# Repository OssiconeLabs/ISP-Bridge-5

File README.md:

# ISP-Bridge-5
ISP Bridge 5(Atmel ATtiny x8, ATmega x8)  
Source files from KiCad 4.0.2-stable, release build
-----
http://ossiconelabs.com  

Available to Buy at https://www.tindie.com/products/OssiconeLabs/isp-bridge-5atmel-attiny-x8-atmega-x8/  
Assembly Instructions at http://ossiconelabs.com/documentation/ISP_Bridge_5_Instructions_v2.0.pdf

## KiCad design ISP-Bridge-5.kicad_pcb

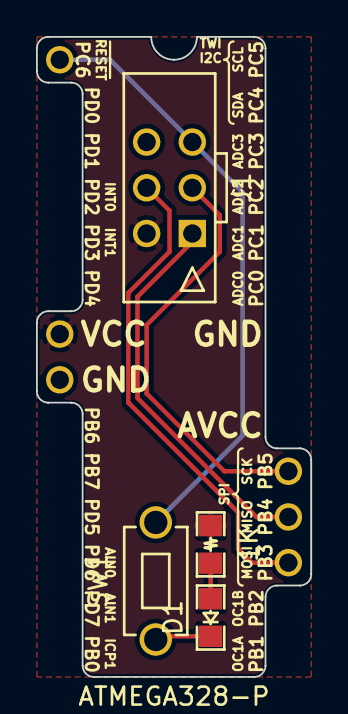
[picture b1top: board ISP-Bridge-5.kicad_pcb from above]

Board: 2 copper layers, 15.2 x 35.6 mm, 6 parts (0 on the bottom side), 7 nets.

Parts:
D1: LED; LED_0805_Symbol
IC1: ATMEGA328-P; Atmel_ATtiny-x8_ATmega-x8
J1: ATMEL_ISP_6PIN; Atmel_ISP_6PIN
R1: 1K; R_0805_Symbol
SW1: SW_PUSH; SW_PUSH_MJTP1250
VAL: REF; Ossicone_Labs_Logo_0.165prop_flipped

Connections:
GND: D1.1, IC1.8, J1.6, SW1.1
unnamed: D1.2, R1.2
unnamed: IC1.1, J1.5, SW1.2
unnamed: IC1.17, J1.4
unnamed: IC1.18, J1.1
unnamed: IC1.19, J1.3
VCC: IC1.7, J1.2, R1.1

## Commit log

2015-08-07 Rev 1.0
2015-08-09 added source file program description
2015-08-09 split lines 2 and 3 with line break
2016-07-04 Update to latest Ossicone Labs Libraries
2016-07-04 Updated to pretty footprint libraries & fixed resister and led symbols
2016-07-04 Updated for KiCad 4.0.2, uses pretty libraries
2016-07-04 Rev 1.1 - changed rev number on board and 16 -> 32 segment on floodfills
2016-07-04 updated tindie link & add link to Assembly Instructions
2016-07-04 updated source file program description
2016-07-04 prevent line 3 from becoming a header
2017-02-01 Remove unused libs, update logo, increase to v1.1
2017-02-02 Removed unused layers
